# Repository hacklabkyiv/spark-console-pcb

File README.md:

# spark-console-pcb
PCB for SPARK - small game console

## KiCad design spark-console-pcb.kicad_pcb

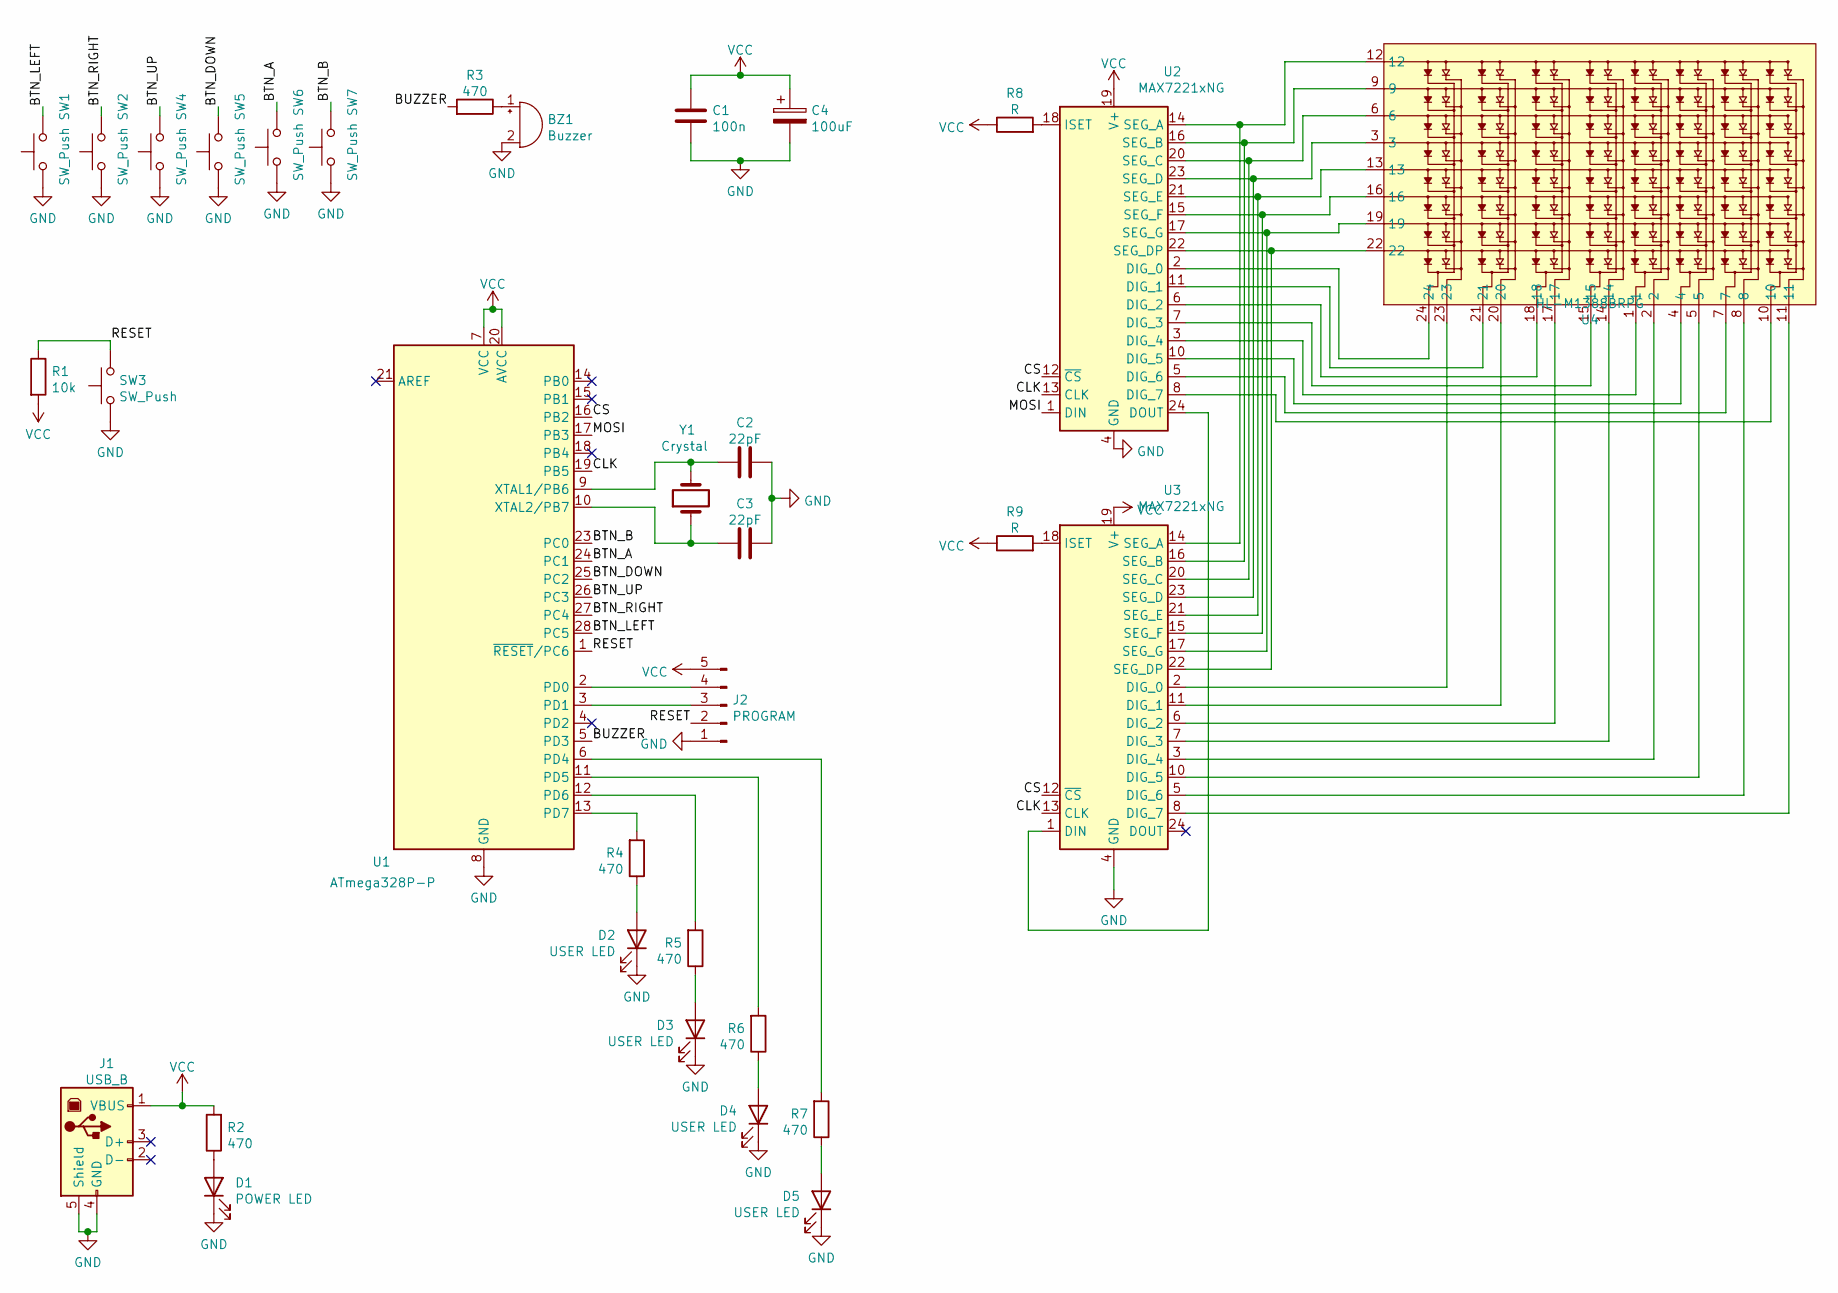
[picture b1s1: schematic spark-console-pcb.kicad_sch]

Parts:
BZ1: Buzzer; Buzzer_15x7.5RM7.6
C1: 100n; C_Disc_D4.7mm_W2.5mm_P5.00mm
C2, C3: 22pF; C_Disc_D4.7mm_W2.5mm_P5.00mm
C4: 100uF; CP_Radial_D6.3mm_P2.50mm
D1: POWER LED; LED_D3.0mm
D2, D3, D4, D5: USER LED; LED_D3.0mm
J1: USB_B; USB_Micro-B_Wuerth_614105150721_Vertical
J2: PROGRAM; PinHeader_1x05_P2.54mm_Horizontal
R1: 10k; R_Axial_DIN0204_L3.6mm_D1.6mm_P7.62mm_Horizontal
R2, R3, R4, R5, R6, R7: 470; R_Axial_DIN0204_L3.6mm_D1.6mm_P7.62mm_Horizontal
R8, R9: R; R_Axial_DIN0204_L3.6mm_D1.6mm_P7.62mm_Horizontal
SW1, SW2, SW4, SW5, SW6, SW7: SW_Push; SW_PUSH-12mm
SW3: SW_Push; SW_PUSH_6mm
U1: ATmega328P-P; DIP-28_W7.62mm
U2, U3: MAX7221xNG; DIP-24_W7.62mm
U4: HL-M1388BRPG
Y1: Crystal; Crystal_HC49-4H_Vertical

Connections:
/BTN_A: SW6.2, U1.24 (PC1)
/BTN_B: SW7.2, U1.23 (PC0)
/BTN_DOWN: SW5.2, U1.25 (PC2)
/BTN_LEFT: SW1.2, U1.28 (PC5)
/BTN_RIGHT: SW2.2, U1.27 (PC4)
/BTN_UP: SW4.2, U1.26 (PC3)
/BUZZER: R3.2, U1.5 (PD3)
/CLK: U1.19 (PB5), U2.13 (CLK), U3.13 (CLK)
/CS: U1.16 (PB2), U2.12 (~CS), U3.12 (~CS)
/MOSI: U1.17 (PB3), U2.1 (DIN)
/RESET: J2.2, R1.1, SW3.2, U1.1 (~RESET~/PC6)
GND: BZ1.2 (+), C1.2, C2.2, C3.2, C4.2, D1.1 (K), D2.1 (K), D3.1 (K), D4.1 (K), D5.1 (K), J1.4 (GND), J1.5 (Shield), J2.1, SW1.1, SW2.1, SW3.1, SW4.1, SW5.1, SW6.1, SW7.1, U1.8 (GND), U1.22 (GND), U2.4 (GND), U2.9 (GND), U3.4 (GND), U3.9 (GND)
unnamed: BZ1.1 (-), R3.1
unnamed: C2.1, U1.9 (XTAL1/PB6), Y1.2
unnamed: C3.1, U1.10 (XTAL2/PB7), Y1.1
unnamed: D1.2 (A), R2.1
unnamed: D2.2 (A), R4.1
unnamed: D3.2 (A), R5.1
unnamed: D4.2 (A), R6.1
unnamed: D5.2 (A), R7.1
unnamed: J2.3, U1.3 (PD1)
unnamed: J2.4, U1.2 (PD0)
unnamed: R4.2, U1.13 (PD7)
unnamed: R5.2, U1.12 (PD6)
unnamed: R6.2, U1.11 (PD5)
unnamed: R7.2, U1.6 (PD4)
unnamed: R8.2, U2.18 (ISET)
unnamed: R9.2, U3.18 (ISET)
unnamed: U2.2 (DIG_0), U4.24
unnamed: U2.3 (DIG_4), U4.1
unnamed: U2.5 (DIG_6), U4.7
unnamed: U2.6 (DIG_2), U4.18
unnamed: U2.7 (DIG_3), U4.15
unnamed: U2.8 (DIG_7), U4.10
unnamed: U2.10 (DIG_5), U4.4
unnamed: U2.11 (DIG_1), U4.21
unnamed: U2.14 (SEG_A), U3.14 (SEG_A), U4.12
unnamed: U2.15 (SEG_F), U3.15 (SEG_F), U4.16
unnamed: U2.16 (SEG_B), U3.16 (SEG_B), U4.9
unnamed: U2.17 (SEG_G), U3.17 (SEG_G), U4.19
unnamed: U2.20 (SEG_C), U3.20 (SEG_C), U4.6
unnamed: U2.21 (SEG_E), U3.21 (SEG_E), U4.13
unnamed: U2.22 (SEG_DP), U3.22 (SEG_DP), U4.22
unnamed: U2.23 (SEG_D), U3.23 (SEG_D), U4.3
unnamed: U2.24 (DOUT), U3.1 (DIN)
unnamed: U3.2 (DIG_0), U4.23
unnamed: U3.3 (DIG_4), U4.2
unnamed: U3.5 (DIG_6), U4.8
unnamed: U3.6 (DIG_2), U4.17
unnamed: U3.7 (DIG_3), U4.14
unnamed: U3.8 (DIG_7), U4.11
unnamed: U3.10 (DIG_5), U4.5
unnamed: U3.11 (DIG_1), U4.20
VCC: C1.1, C4.1, J1.1 (VBUS), J2.5, R1.2, R2.2, R8.1, R9.1, U1.7 (VCC), U1.20 (AVCC), U2.19 (V+), U3.19 (V+)

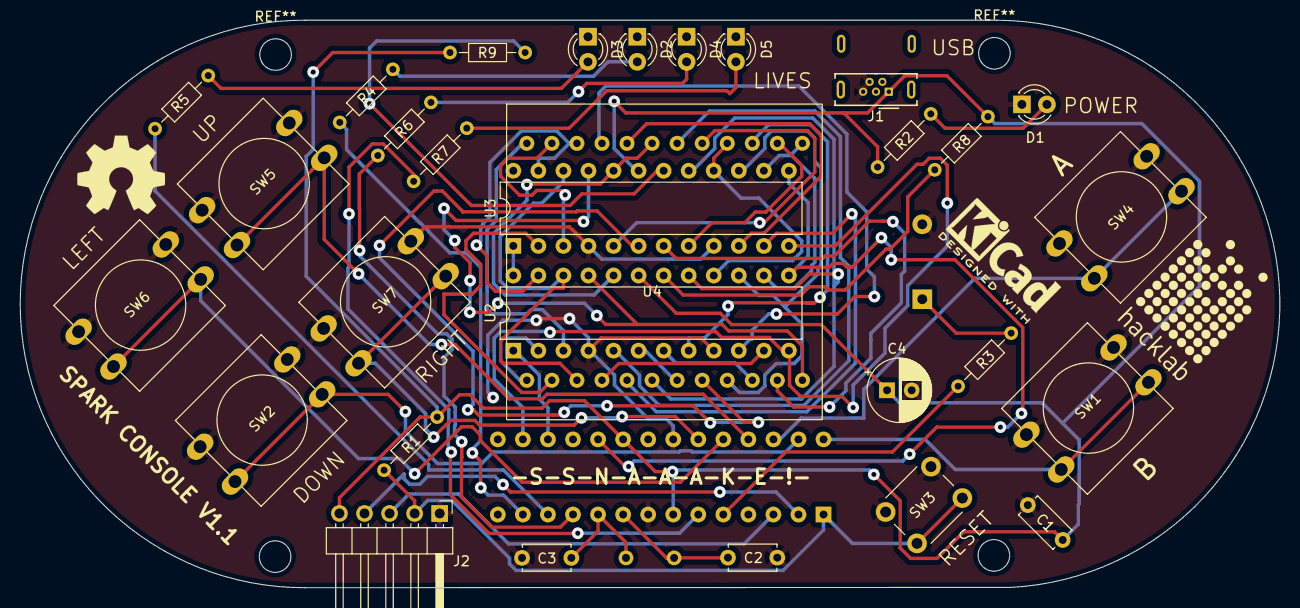
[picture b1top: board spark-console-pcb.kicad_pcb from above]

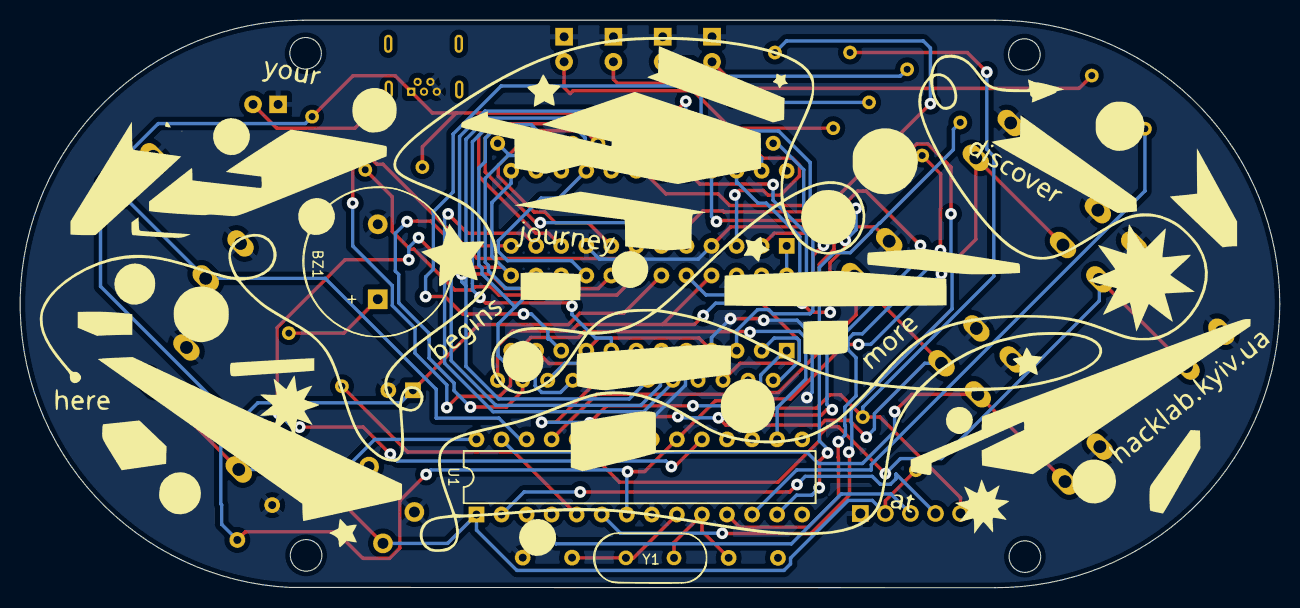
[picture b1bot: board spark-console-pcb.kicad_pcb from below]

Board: 2 copper layers, 127.7 x 57.5 mm, 33 parts (3 on the bottom side), 54 nets.

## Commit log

2021-04-06 Added KiCad project files
2021-04-06 Added HL-M1388BRPG bi-color matrix symbol
2021-04-06 Finished first version of schematics
2021-04-06 Added footprint for HL-M1388BRPG bi-color led matrix
2021-04-06 Associated symbols and footprints
2021-04-06 Fix MAX7221 footprint
2021-04-07 Added first version of PCB
2021-04-08 Spark v0.0.1
2021-04-13 Changes from lazerninja
